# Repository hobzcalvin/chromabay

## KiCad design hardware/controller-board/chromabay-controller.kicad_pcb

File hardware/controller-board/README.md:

# ChromaBay Controller (rev A)

A battery-powered ESP32-S3 LED controller: USB-C charging with a power path, a 5 V / 2 A LED rail, 4 clock+data
outputs (or 8 single-wire), a PDM mic, a 6-axis IMU, a swappable JST-PH battery and solder-free push-in LED terminals, on
36 × 66 mm (1.6 mm, rounded nose) with the button, USB-C and power switch all at one end, flush with the case
face (the button and switch stick out past it on their own).
The design reasoning is in [DESIGN.md](DESIGN.md). **Interactive 3D mock:** [viewer/index.html](viewer/index.html)
(needs the model files; see "Regenerate").

**Status:** schematic complete and ERC-clean. **Board fully routed:** DRC shows 0 errors and 0 unrouted. The charger
and boost power stage is hand-laid-out with copper pours (`tools/power_layout.py`), and the rest is autorouted. See
DESIGN.md section 0g. Before ordering: review it in KiCad and check part rotations in JLC's 3D preview.

| | |
|---|---|
|  |  |
|  |  |

## Files

| Path | What |
|---|---|
| `chromabay-controller.kicad_pro/.kicad_sch/.kicad_pcb` | KiCad 9 project. Open the `.kicad_pro`. |
| `chromabay-controller-schematic.pdf` | Schematic PDF |
| `lib/lcsc.*` | Symbols, footprints and 3D models for the exact JLC/LCSC parts (via easyeda2kicad) |
| `lib/cb.pretty` | Board-specific footprints: LED output pads, battery pads |
| `tools/design.py` | **Single source of truth**: every part, LCSC code and net |
| `tools/outline.py` | Board outline (rounded nose, battery notch), shared by the board and the case |
| `tools/gen_sch.py`, `tools/gen_pcb.py` | Generate the schematic and the placed board from `design.py` |
| `tools/jlc_cost.py`, `tools/jlc_lookup.py` | Live JLC prices / Basic-vs-Extended status, and the order cost estimate |
| `tools/jlc_files.py` → `fab/` | JLC BOM + CPL for each build: `complete`, `plug`, `core` |
| `tools/cost_options.py` | What each optional feature costs per board |
| `case/case.py` → `case/out/*.stl` | Parametric clamshell case: `external`, `slim` (603450 cell), `thick` (103450 cell), `brick` (2 × 18650) |
| `tools/route.py` | Autoroute: GND fan-out, DSN export (In1 kept as plane), Freerouting 1.9, SES import, zone fill |
| `tools/power_layout.py` | Hand layout of the charger/boost power copper: pours, In2 plane regions, via arrays, short links |
| `tools/fix_silk.py` | Nudges user-header labels off vias, pads and part outlines on the routed board (re-run after regenerating) |
| `tools/fanout.py`, `tools/patch_route.py` | GND via fan-out; small maze router for leftover gaps (+ via merge) |
| `tools/label_render.py` | Labeled top-view render |
| `renders/` | Board renders (KiCad), labeled interaction-point view, case/battery renders (three.js) |
| `viewer/index.html` | Rotatable 3D mock: board + case variants + clickable connection markers |

## Regenerate

```sh
# KiCad 9 (kicad-cli + its python), easyeda2kicad, cadquery
python3 tools/gen_sch.py && kicad-cli sch erc ../chromabay-controller.kicad_sch   # from tools/
/usr/bin/python3 tools/gen_pcb.py        # KiCad's system python (has pcbnew)
python3 tools/jlc_files.py               # fab/bom-jlc.csv, fab/cpl-jlc.csv
python3 tools/jlc_cost.py 5 10 30        # live cost table
python3 case/case.py                     # case STLs (add STEP by editing the export list)
```

`gen_pcb.py` re-places everything, so **once routing starts, stop regenerating the PCB**: from then on, edit the
schematic in KiCad and use *Update PCB from Schematic*. The symbol/footprint UUID links already match.

## Before ordering

Ready to upload: `fab/gerbers-jlc.zip` (Gerbers + drill), `fab/bom-jlc-<build>.csv` and
`fab/cpl-jlc-<build>.csv` for the build you want (`complete`, `plug` or `core`). Regenerate the Gerbers after any
board edit (see DESIGN.md).

1. Look over the board in KiCad, especially the charger corner by the USB-C.
2. At JLC: 4 layers, 1.6 mm, tented vias, "Economic" PCBA on the top side. In the parts-placement preview, check
   **every** part's rotation and position. The easyeda2kicad parts are usually right, but the USB-C, slide
   switch, button, LED, WAGOs, JST, mic and the QFN/DFN power chips are the ones to look at.
3. Expect JLC to ask about the button and switch overhanging the board edge (on purpose) and the 0.35/0.2 mm
   REGN vias.
4. Boost compensation (15k / 4.7 nF / 47 pF) and current limit (200k) are checked by `tools/boost_loop.py` (the WEBENCH-equivalent loop analysis); no WEBENCH run needed.
5. Order 2–5 to validate. Tests: charge current per jumper setting, boost ripple and efficiency at 2 A, run while
   charging from a weak port, reverse-battery protection, 8 outputs, mic, IMU, deep-sleep current with the switch off.

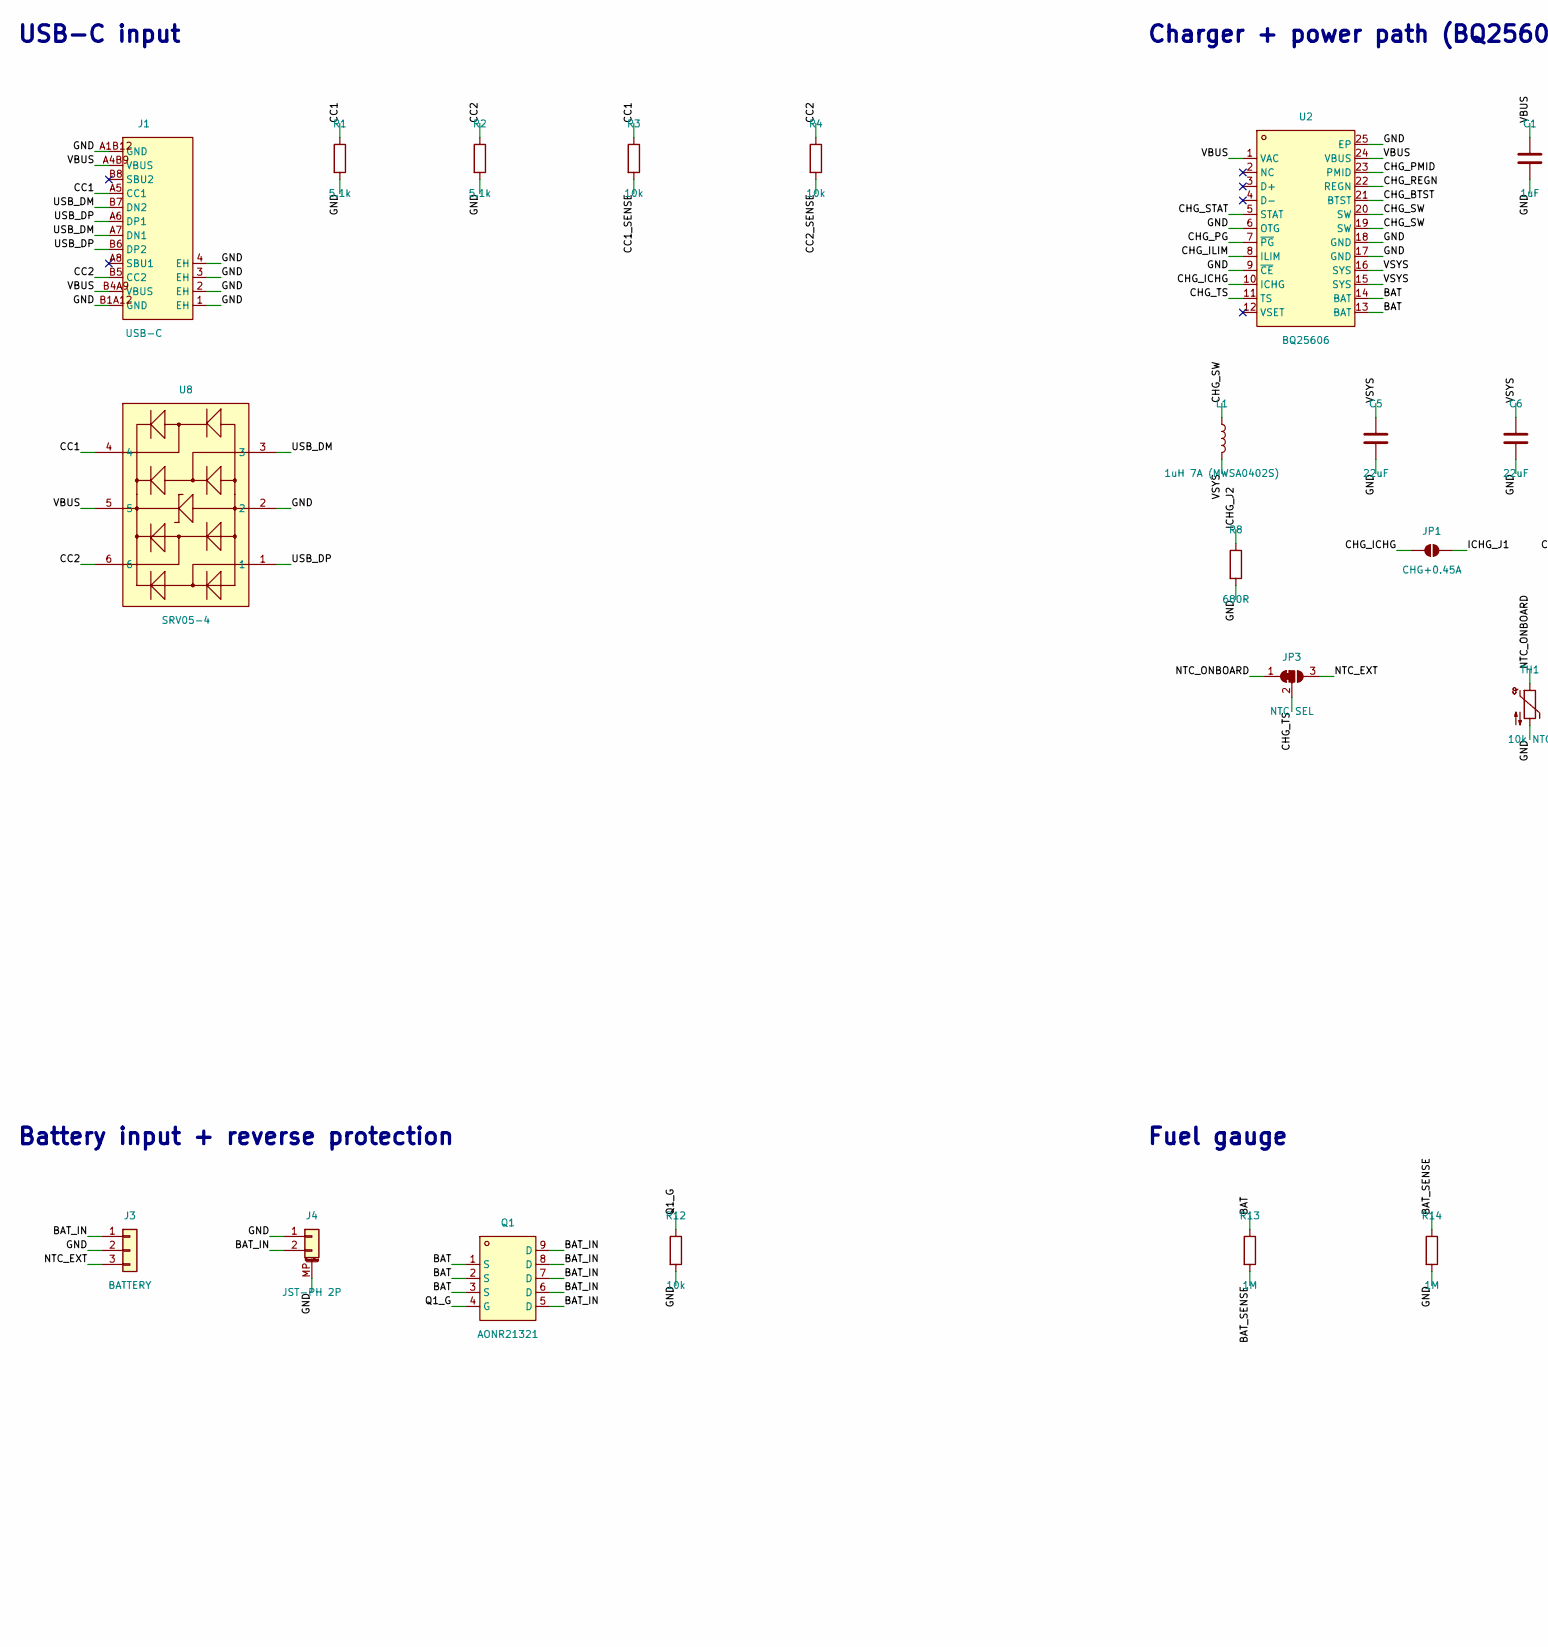
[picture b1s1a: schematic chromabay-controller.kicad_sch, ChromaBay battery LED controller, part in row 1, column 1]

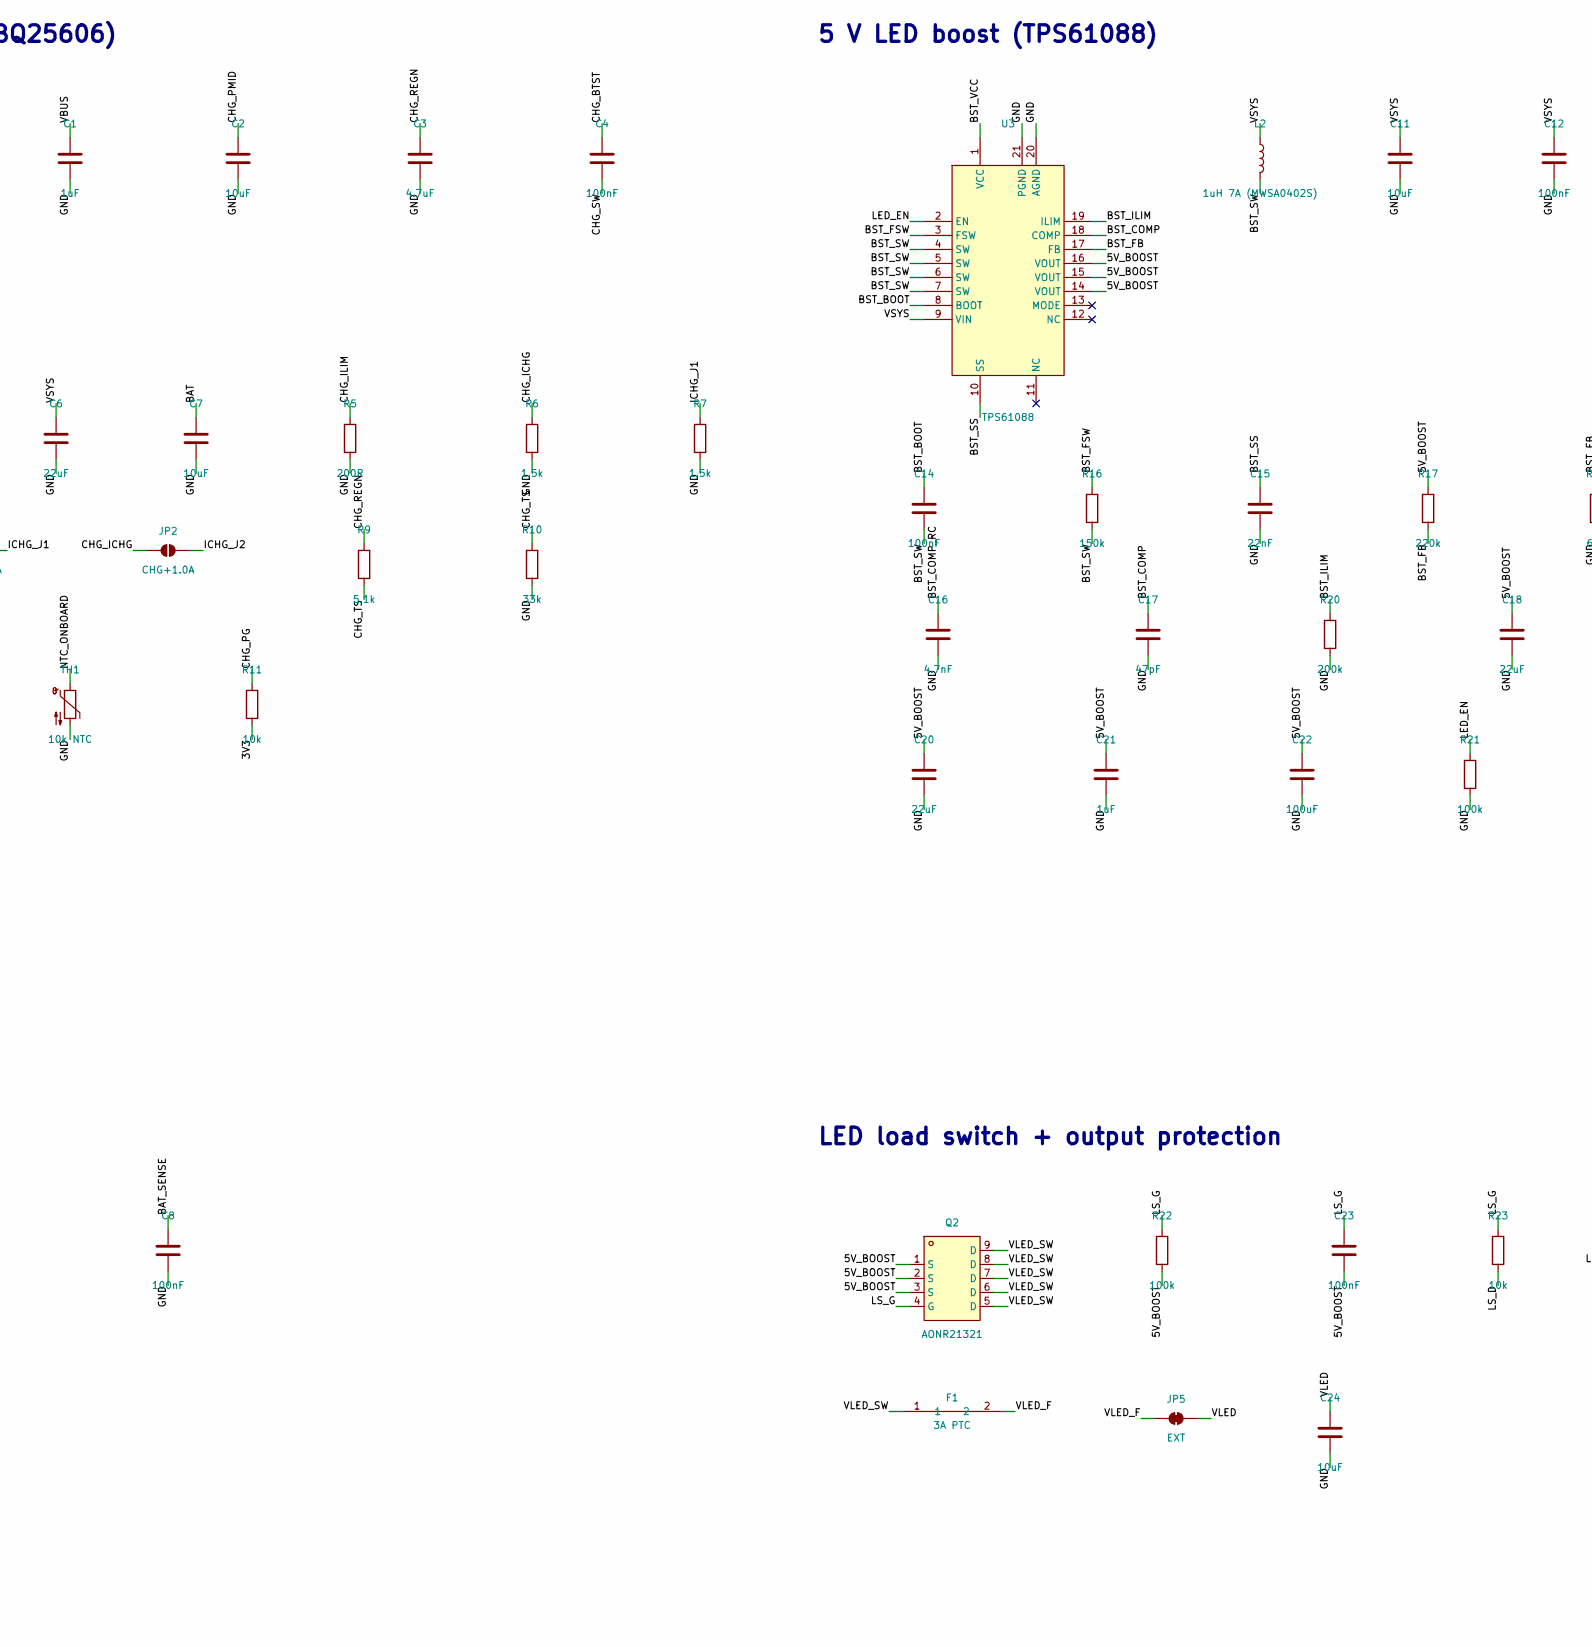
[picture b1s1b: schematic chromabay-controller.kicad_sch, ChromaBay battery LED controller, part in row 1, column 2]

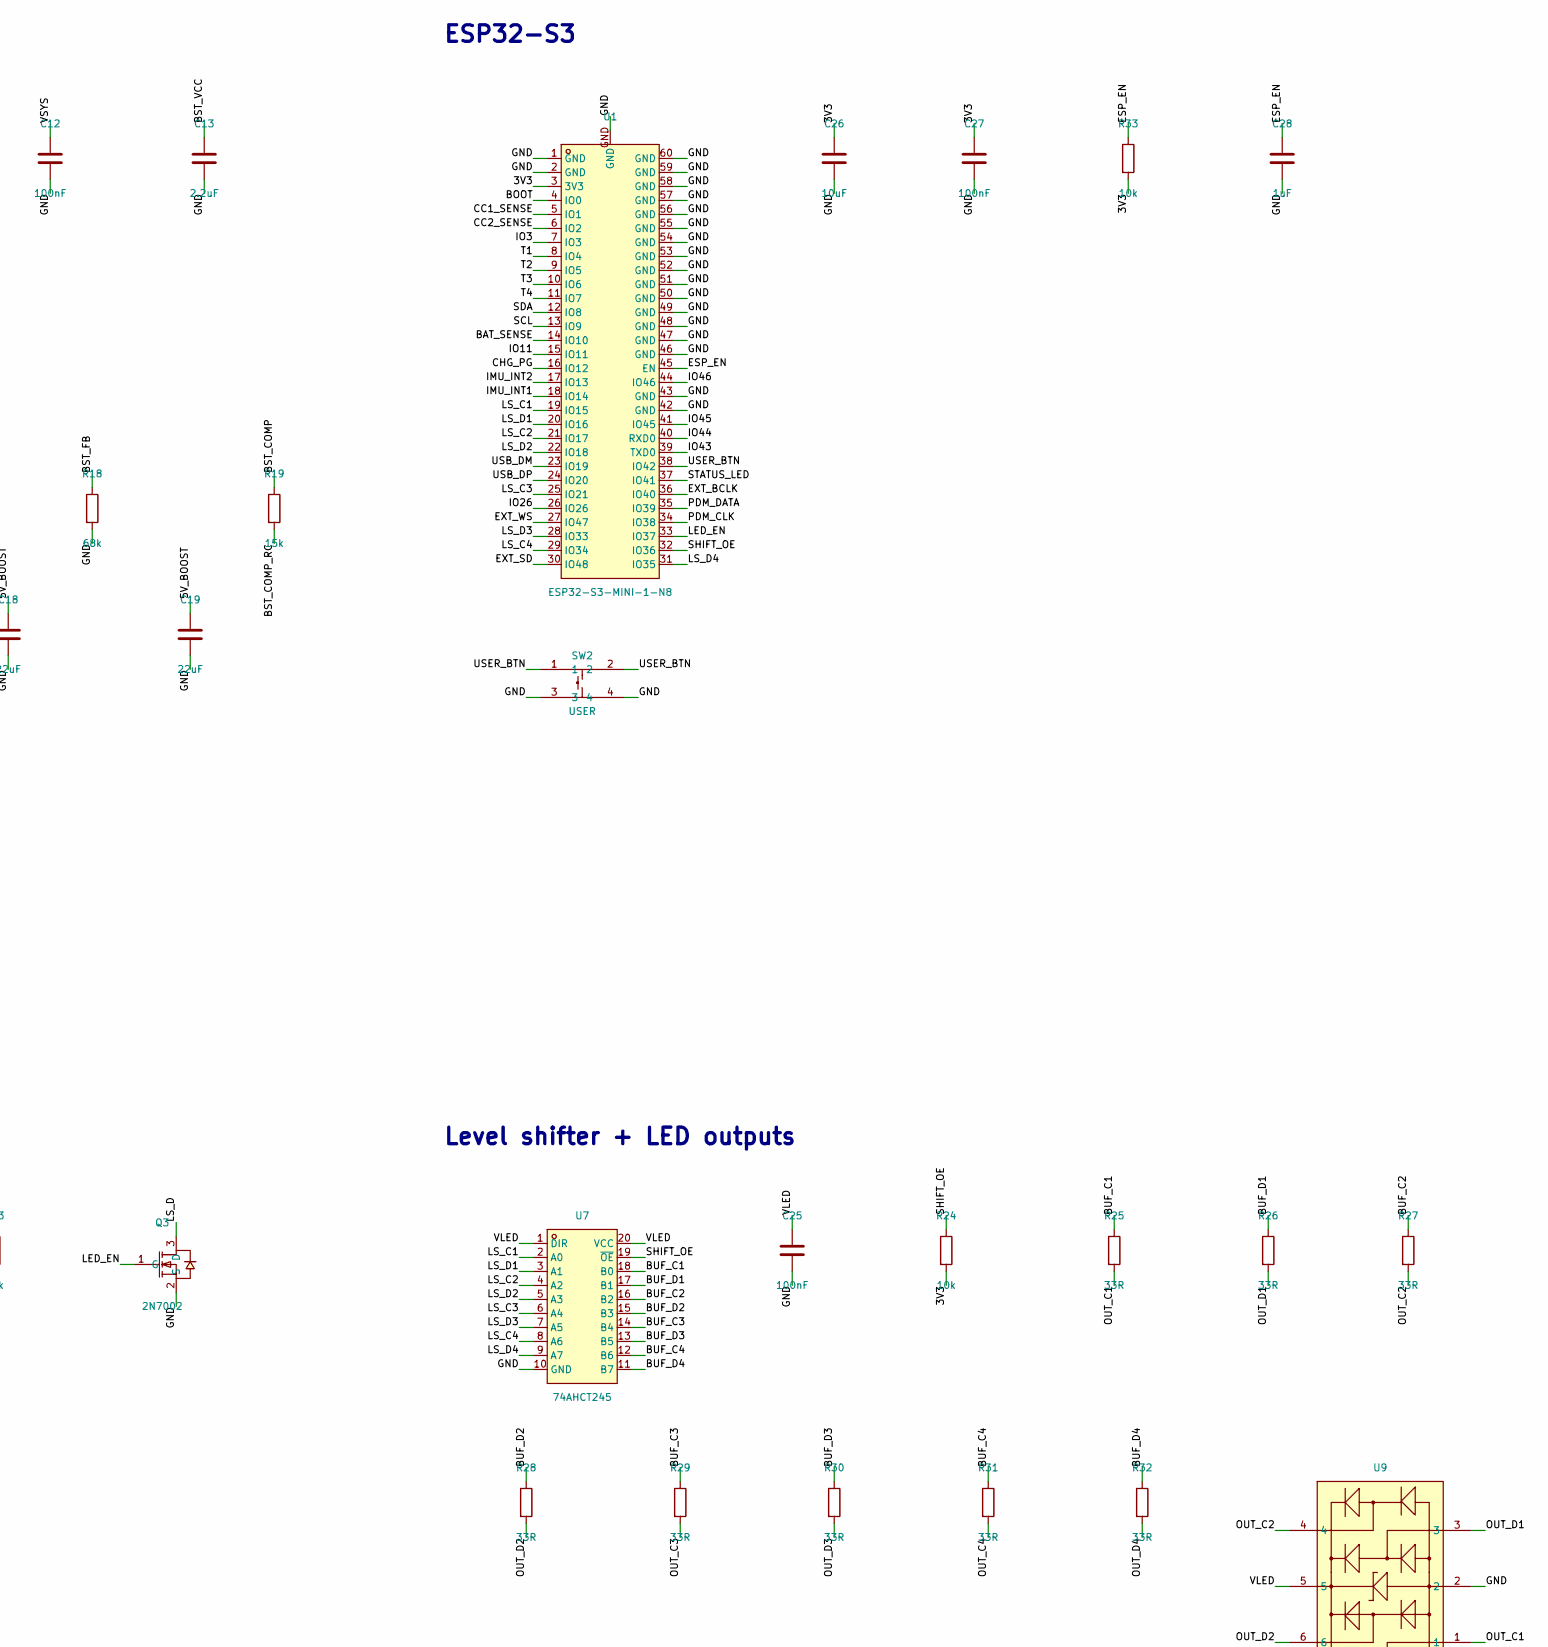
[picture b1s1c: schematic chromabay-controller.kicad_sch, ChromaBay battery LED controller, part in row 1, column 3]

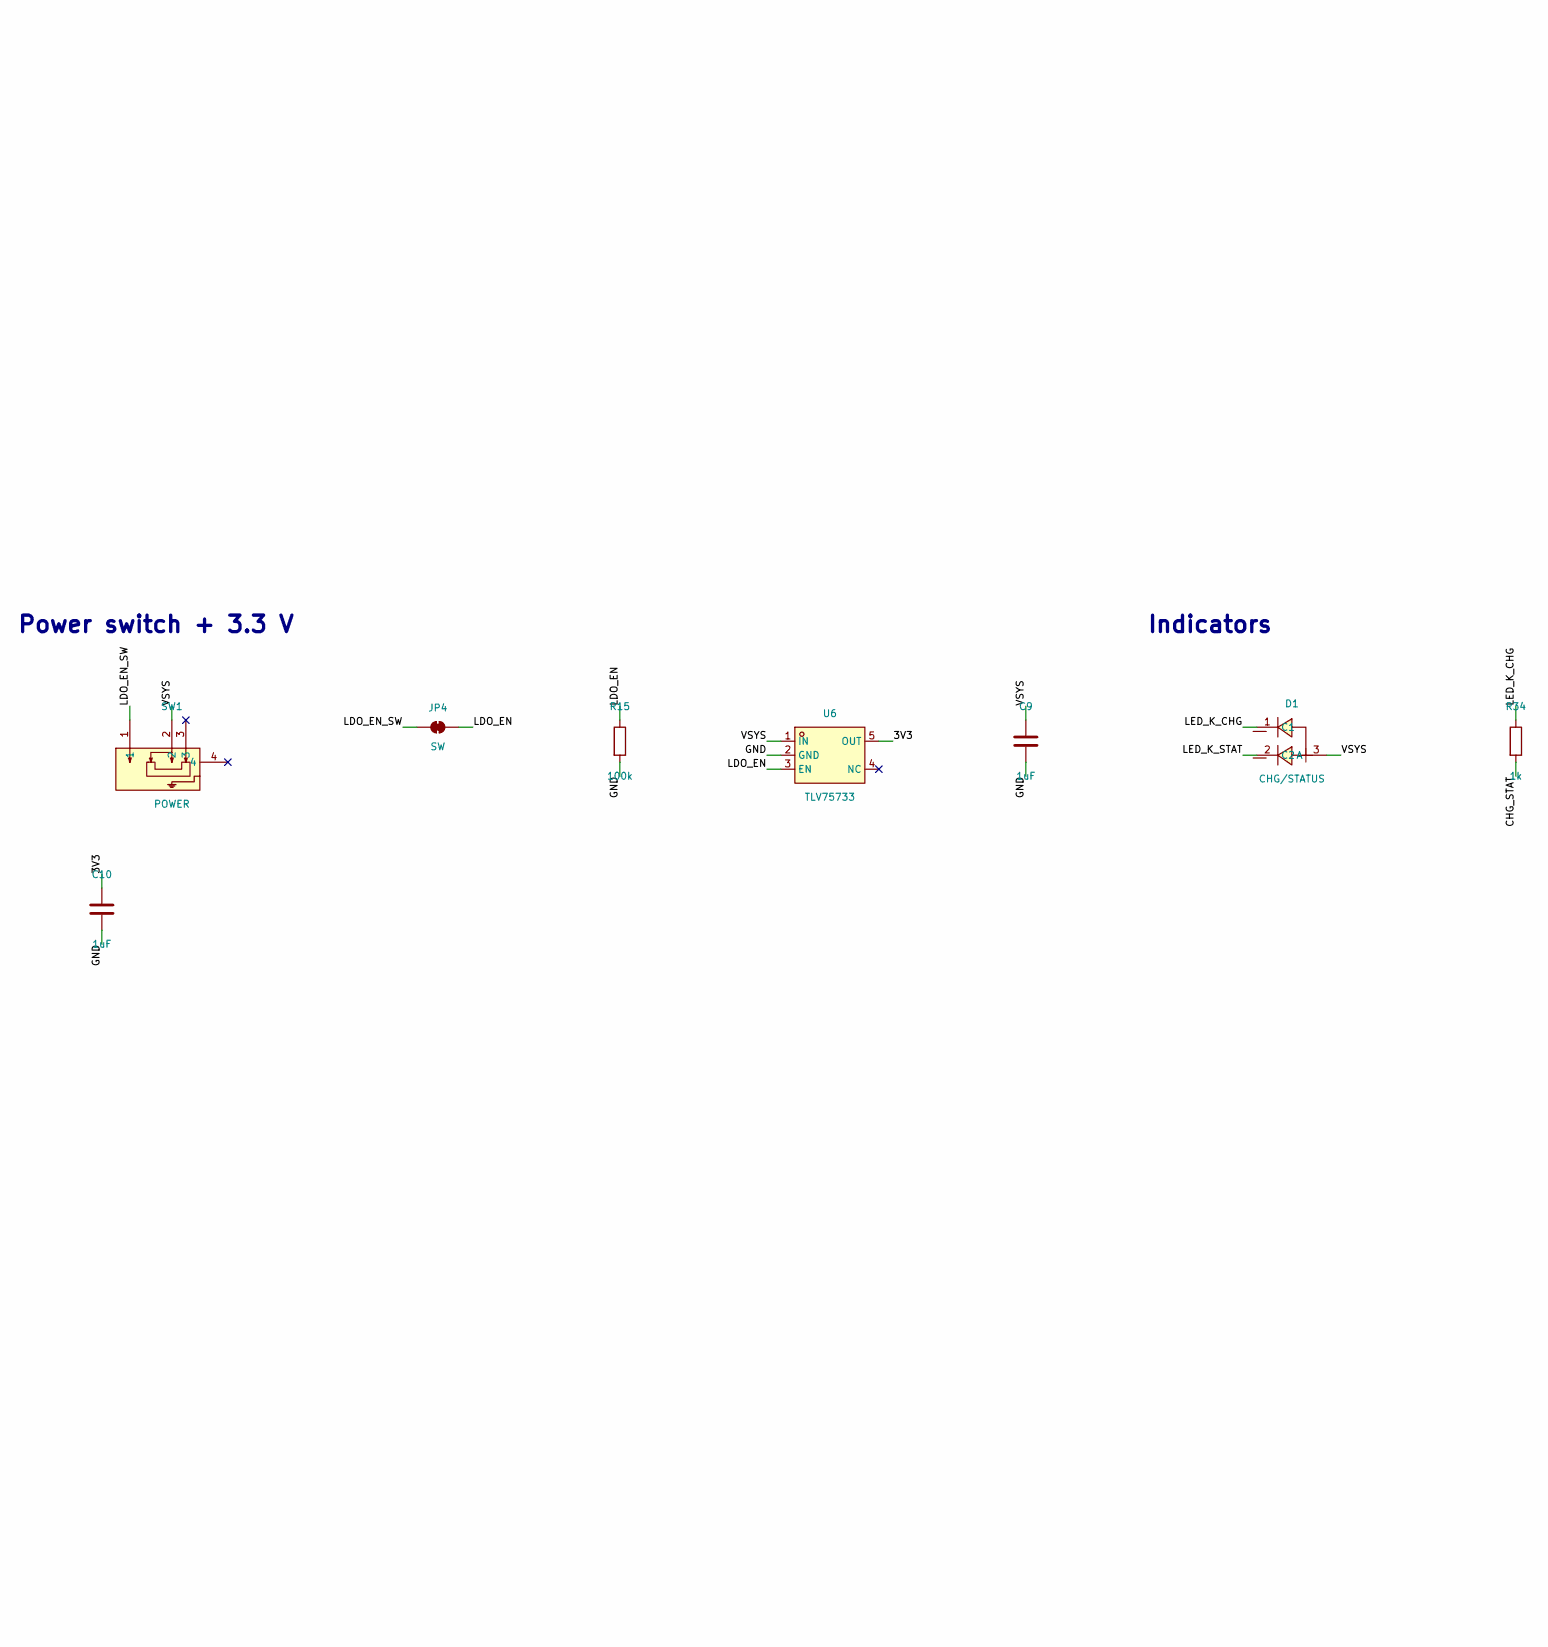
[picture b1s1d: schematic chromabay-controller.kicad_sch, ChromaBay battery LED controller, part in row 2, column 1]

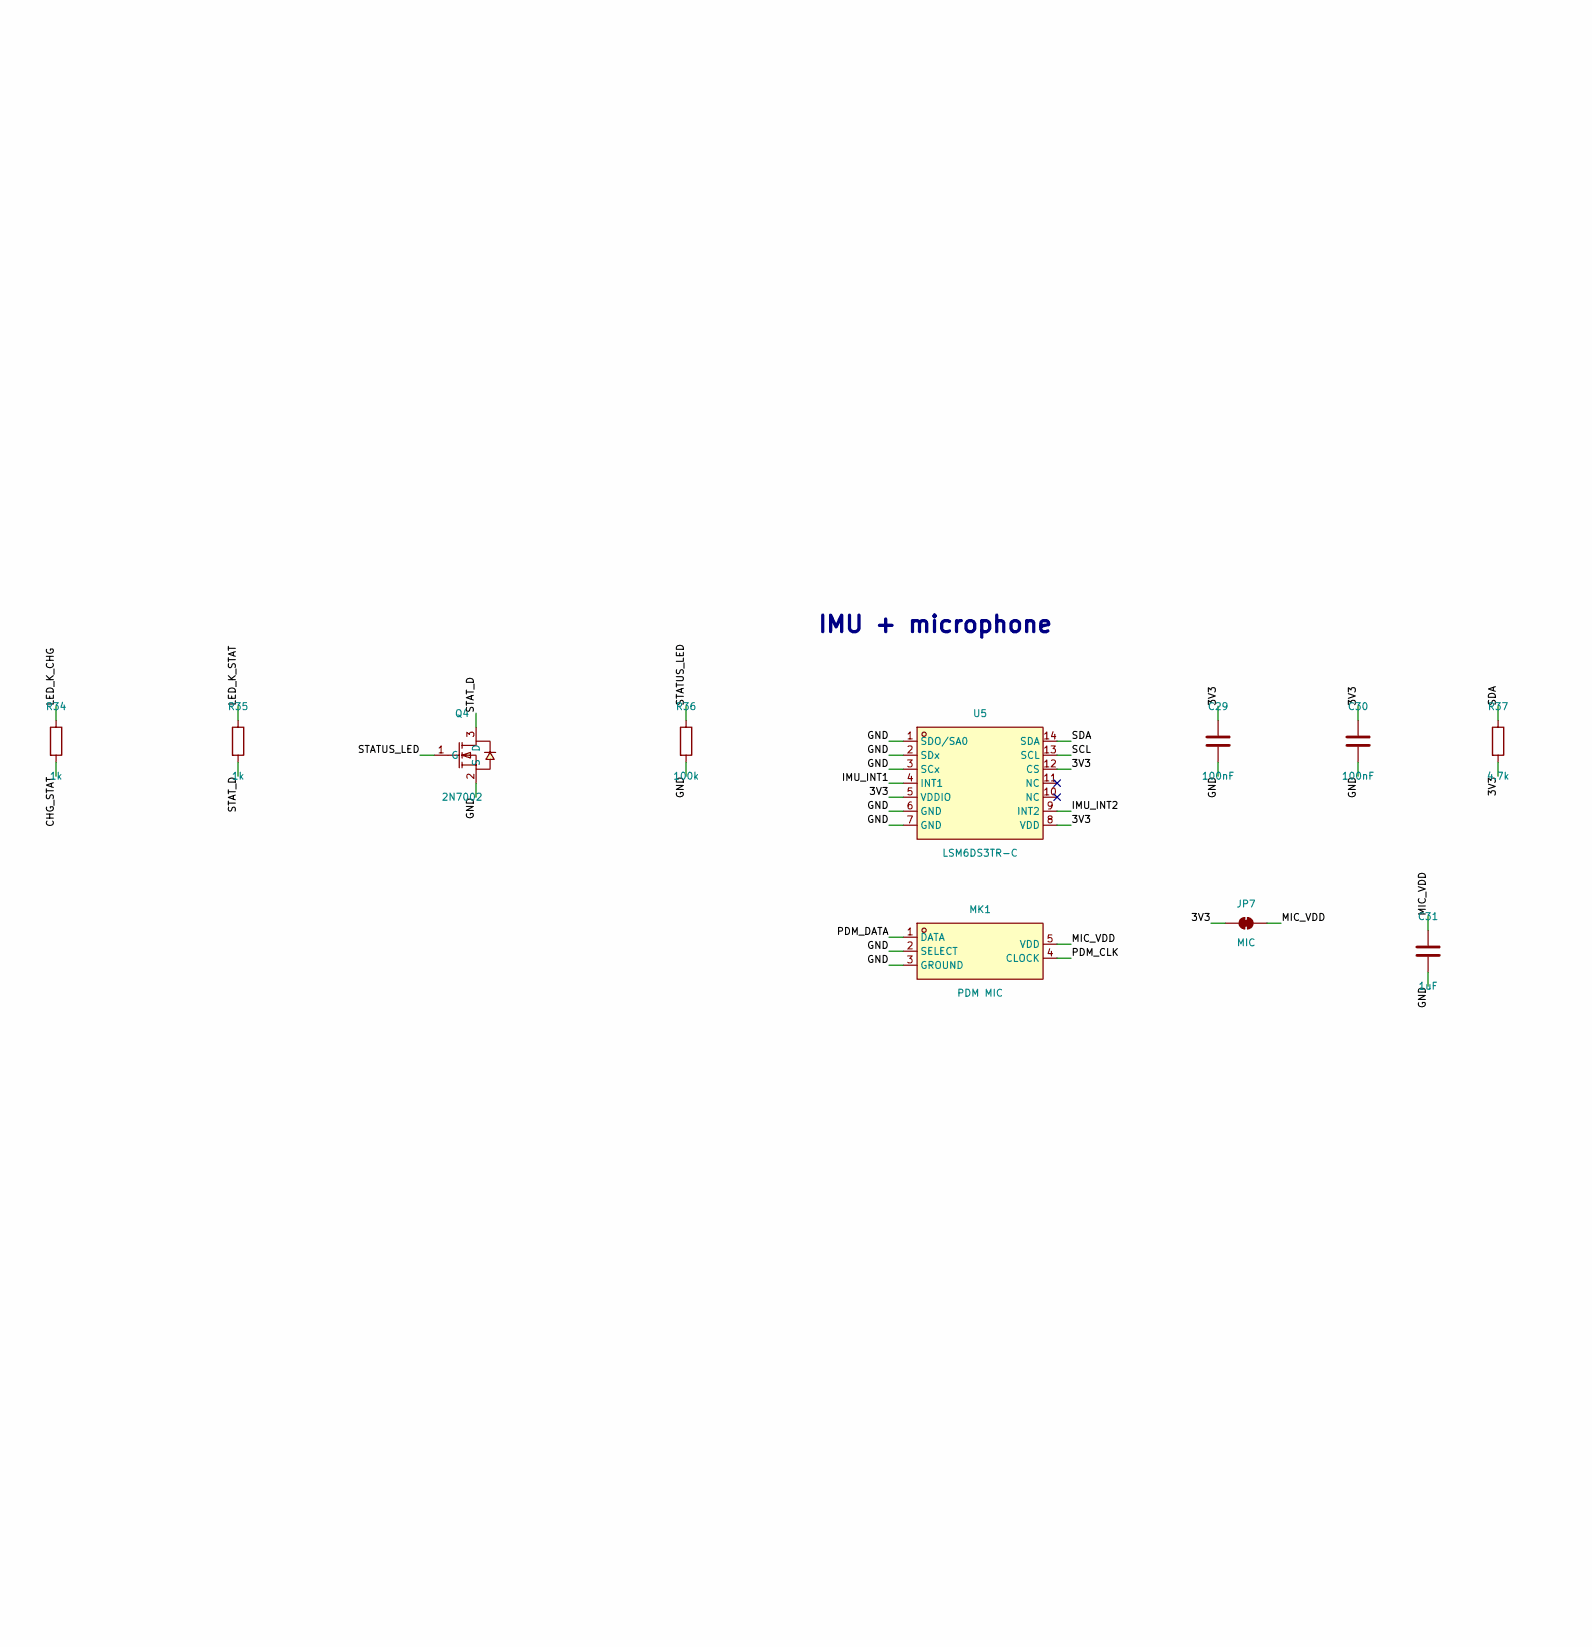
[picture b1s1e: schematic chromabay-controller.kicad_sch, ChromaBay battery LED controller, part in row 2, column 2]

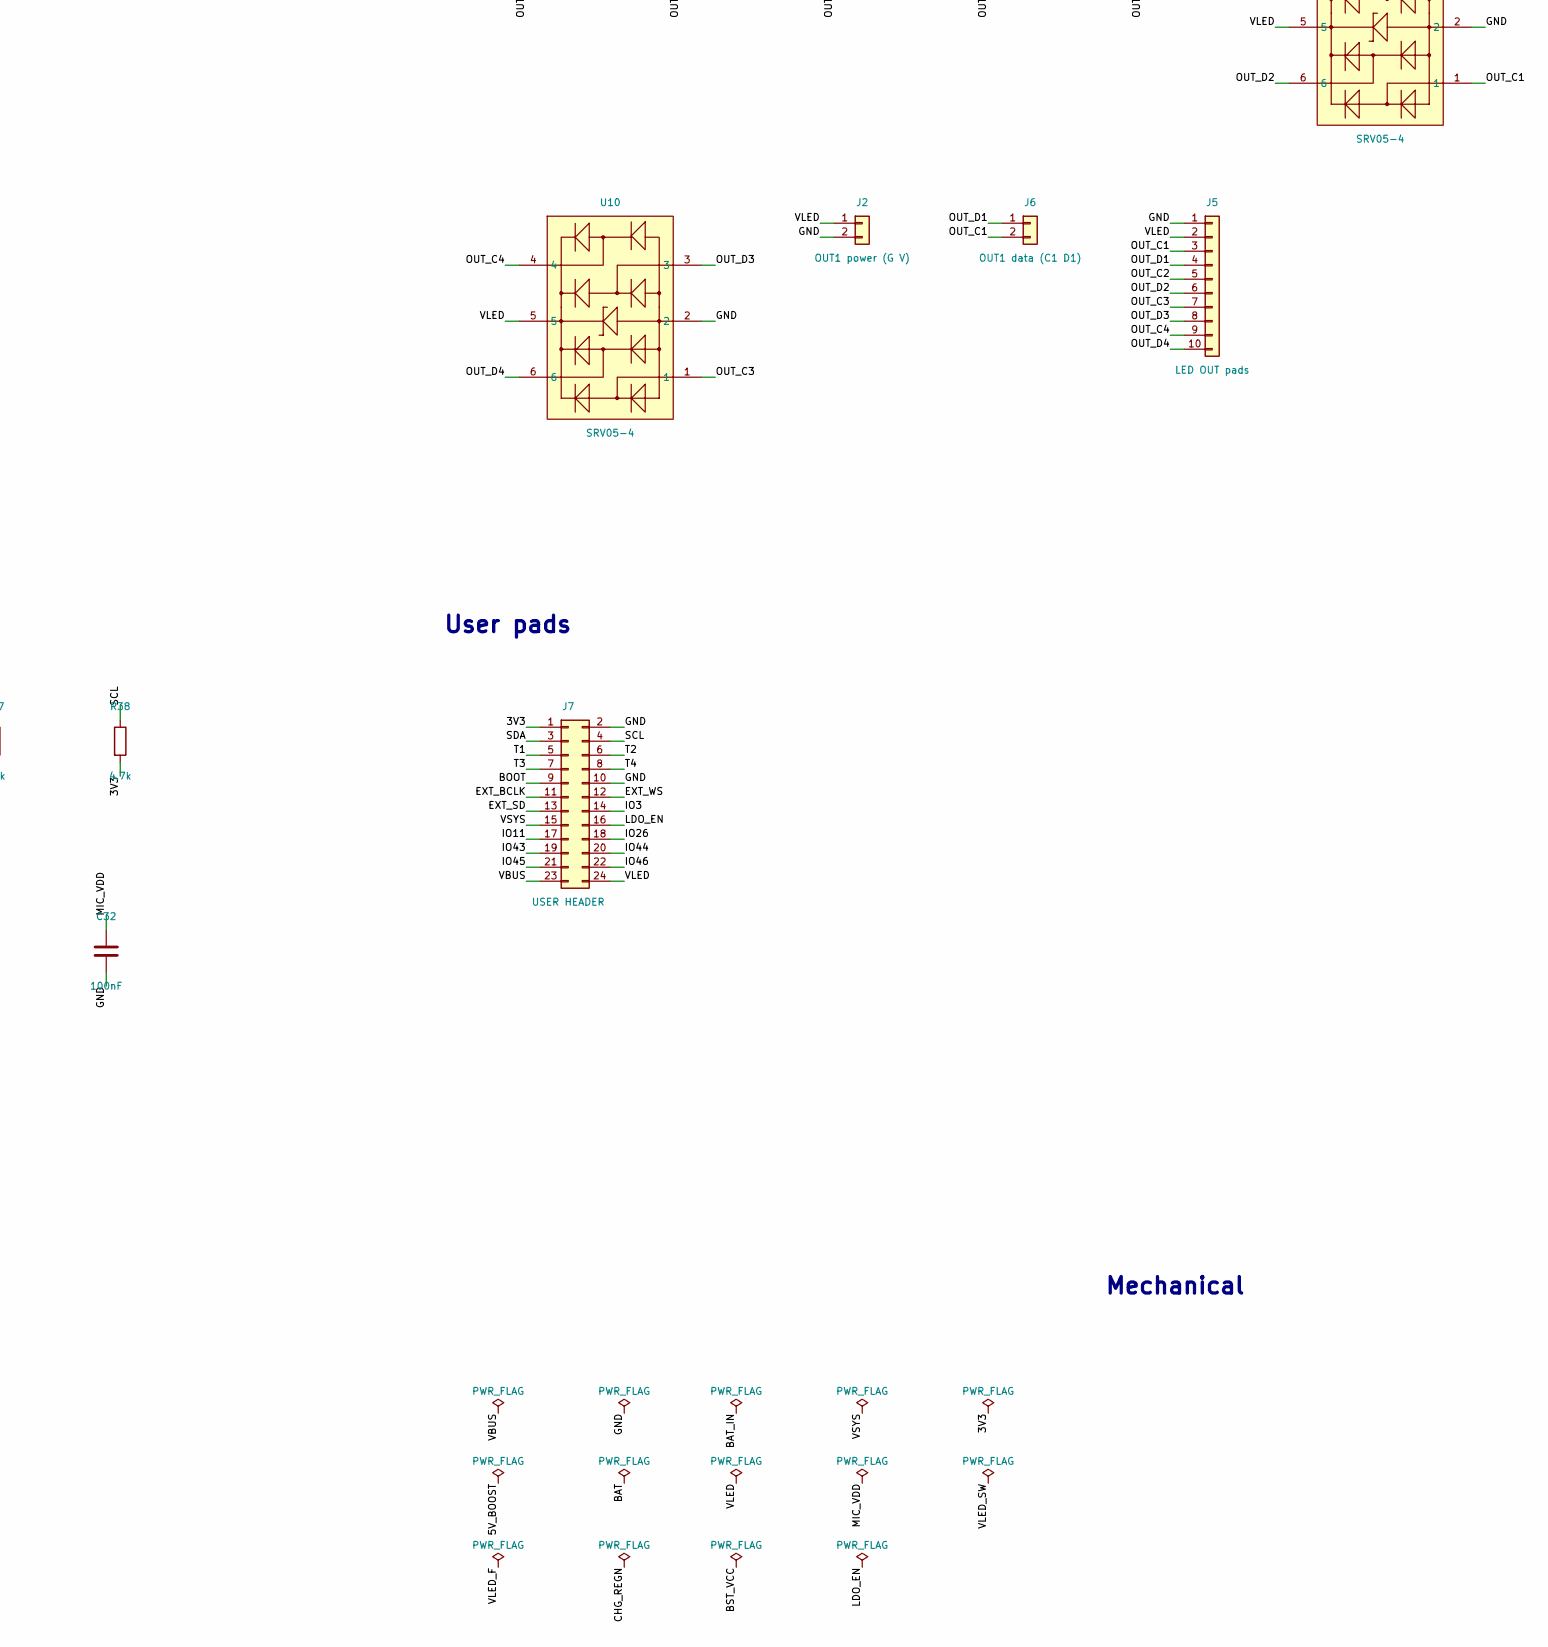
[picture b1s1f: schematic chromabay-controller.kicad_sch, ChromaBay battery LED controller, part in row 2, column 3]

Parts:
C1: 1uF; C0603; LCSC C15849
C2, C7, C11, C24: 10uF; C0805; LCSC C15850
C3: 4.7uF; C0603; LCSC C19666
C4, C8, C12, C14, C23, C25, C27, C29, C30, C32: 100nF; C0402; LCSC C1525
C5, C6, C18, C19, C20: 22uF; C0805; LCSC C45783
C9, C10, C21, C28, C31: 1uF; C0402; LCSC C52923
C13: 2.2uF; C0402; LCSC C12530
C15: 22nF; C0402; LCSC C1532
C16: 4.7nF; C0402; LCSC C1538
C17: 47pF; C0402; LCSC C1567
C22: 100uF; C1206; LCSC C15008
C26: 10uF; C0603; LCSC C19702
D1: CHG/STATUS; LED-SMD_LTST-S326KGJRKT; LCSC C125116
F1: 3A PTC; F1812; LCSC C21004
J1: USB-C; USB-C_SMD-TYPE-C-31-M-12_1; LCSC C165948
J2: OUT1 power (G V); CONN-SMD_2060-452; LCSC C2765055
J3: BATTERY; BatteryPadsSmall
J4: JST-PH 2P; CONN-SMD_P2.00_S2B-PH-SM4-TB-LF-SN; LCSC C54582899
J5: LED OUT pads; OutputPads
J6: OUT1 data (C1 D1); CONN-SMD_2060-452; LCSC C2765055
J7: USER HEADER; PinHeader_2x12_P2.54mm_Vertical
JP1: CHG+0.45A; SolderJumper-2_P1.3mm_Open_RoundedPad1.0x1.5mm
JP2: CHG+1.0A; SolderJumper-2_P1.3mm_Open_RoundedPad1.0x1.5mm
JP3: NTC SEL; SolderJumper-3_P1.3mm_Bridged12_RoundedPad1.0x1.5mm
JP4: SW; SolderJumper-2_P1.3mm_Bridged_RoundedPad1.0x1.5mm
JP5: EXT; SolderJumper-2_P1.3mm_Bridged_RoundedPad1.0x1.5mm
JP7: MIC; SolderJumper-2_P1.3mm_Bridged_RoundedPad1.0x1.5mm
L1, L2: 1uH 7A (MWSA0402S); IND-SMD_L4.4-W4.2; LCSC C408332
MK1: PDM MIC; MIC-SMD_GMA3526H10-B26; LCSC C498192
Q1, Q2: AONR21321; DFN-8_L3.0-W3.0-P0.65-BL; LCSC C541711
Q3, Q4: 2N7002; SOT-23-3_L2.9-W1.3-P1.90-LS2.4-BR; LCSC C8545
R1, R2, R9: 5.1k; R0402; LCSC C25905
R3, R4, R11, R12, R23, R24, R33: 10k; R0402; LCSC C25744
R5: 200R; R0402; LCSC C25087
R6, R7: 1.5k; R0402; LCSC C25867
R8: 680R; R0402; LCSC C25130
R10: 33k; R0402; LCSC C25779
R13, R14: 1M; R0402; LCSC C26083
R15, R21, R22, R36: 100k; R0402; LCSC C25741
R16: 150k; R0402; LCSC C25755
R17: 220k; R0402; LCSC C25767
R18: 68k; R0402; LCSC C36871
R19: 15k; R0402; LCSC C25756
R20: 200k; R0402; LCSC C25764
R25, R26, R27, R28, R29, R30, R31, R32: 33R; R0402; LCSC C25105
R34, R35: 1k; R0402; LCSC C11702
R37, R38: 4.7k; R0402; LCSC C25900
SW1: POWER; SW-TH_MSK12C02; LCSC C431540
SW2: USER; KEY-SMD_4P-L4.8-W4.6-P1.70-LS6.2; LCSC C136662
TH1: 10k NTC; R0402; LCSC C77131
U1: ESP32-S3-MINI-1-N8; BULETM-SMD_ESP32-S3-MINI-1-N8; LCSC C2913206
U2: BQ25606; VQFN-24_L4.0-W4.0-P0.50-TL-EP2.8; LCSC C374063
U3: TPS61088; VQFN-20_L4.6-W3.6-P0.50-BL; LCSC C87357
U5: LSM6DS3TR-C; LGA-14_L3.0-W2.5-P0.50-TL; LCSC C967633
U6: TLV75733; SOT-23-5_L2.9-W1.6-P0.95-LS2.8-BL; LCSC C485517
U7: 74AHCT245; TSSOP-20_L6.5-W4.4-P0.65-LS6.4-BL; LCSC C54815895
U8, U9, U10: SRV05-4; SOT-23-6_L2.9-W1.6-P0.95-LS2.8-BR; LCSC C85364

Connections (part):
/3V3: C10.1, C26.1, C27.1, C29.1, C30.1, J7.1, JP7.1 (A), R11.2, R24.2, R33.2, R37.2, R38.2, U1.3 (3V3), U5.5 (VDDIO), U5.8 (VDD), U5.12 (CS), U6.5 (OUT)
/5V_BOOST: C18.1, C19.1, C20.1, C21.1, C22.1, C23.2, Q2.1 (S), Q2.2 (S), Q2.3 (S), R17.1, R22.2, U3.14 (VOUT), U3.15 (VOUT), U3.16 (VOUT)
/BAT: C7.1, Q1.1 (S), Q1.2 (S), Q1.3 (S), R13.1, U2.13 (BAT), U2.14 (BAT)
/BAT_IN: J3.1, J4.2, Q1.5 (D), Q1.6 (D), Q1.7 (D), Q1.8 (D), Q1.9 (D)
/BAT_SENSE: C8.1, R13.2, R14.1, U1.14 (IO10)
/BOOT: J7.9, U1.4 (IO0)
/BST_BOOT: C14.1, U3.8 (BOOT)
/BST_COMP: C17.1, R19.1, U3.18 (COMP)
/BST_COMP_RC: C16.1, R19.2
/BST_FB: R17.2, R18.1, U3.17 (FB)
/BST_FSW: R16.1, U3.3 (FSW)
/BST_ILIM: R20.1, U3.19 (ILIM)
/BST_SS: C15.1, U3.10 (SS)
/BST_SW: C14.2, L2.2, R16.2, U3.4 (SW), U3.5 (SW), U3.6 (SW), U3.7 (SW)
/BST_VCC: C13.1, U3.1 (VCC)
/BUF_C1: R25.1, U7.18 (B0)
/BUF_C2: R27.1, U7.16 (B2)
/BUF_C3: R29.1, U7.14 (B4)
/BUF_C4: R31.1, U7.12 (B6)
/BUF_D1: R26.1, U7.17 (B1)
/BUF_D2: R28.1, U7.15 (B3)
/BUF_D3: R30.1, U7.13 (B5)
/BUF_D4: R32.1, U7.11 (B7)
/CC1: J1.A5 (CC1), R1.1, R3.1, U8.4
/CC1_SENSE: R3.2, U1.5 (IO1)
/CC2: J1.B5 (CC2), R2.1, R4.1, U8.6
/CC2_SENSE: R4.2, U1.6 (IO2)
/CHG_BTST: C4.1, U2.21 (BTST)
/CHG_ICHG: JP1.1 (A), JP2.1 (A), R6.1, U2.10 (ICHG)
/CHG_ILIM: R5.1, U2.8 (ILIM)
/CHG_PG: R11.1, U1.16 (IO12), U2.7 (~PG)
/CHG_PMID: C2.1, U2.23 (PMID)
/CHG_REGN: C3.1, R9.1, U2.22 (REGN)
/CHG_STAT: R34.2, U2.5 (STAT)
/CHG_SW: C4.2, L1.1, U2.19 (SW), U2.20 (SW)
/CHG_TS: JP3.2 (C), R9.2, R10.1, U2.11 (TS)
/ESP_EN: C28.1, R33.1, U1.45 (EN)
/EXT_BCLK: J7.11, U1.36 (IO40)
/EXT_SD: J7.13, U1.30 (IO48)
/EXT_WS: J7.12, U1.27 (IO47)
/GND: C1.2, C2.2, C3.2, C5.2, C6.2, C7.2, C8.2, C9.2, C10.2, C11.2, C12.2, C13.2, C15.2, C16.2, C17.2, C18.2, C19.2, C20.2, C21.2, C22.2, C24.2, C25.2, C26.2, C27.2, C28.2, C29.2, C30.2, C31.2, C32.2, J1.1 (EH), J1.2 (EH), J1.3 (EH), J1.4 (EH), J1.A1B12 (GND), J1.B1A12 (GND), J2.2, J3.2, J4.1, J4.MP (MountPin), J5.1, J7.2, J7.10, MK1.2 (SELECT), MK1.3 (GROUND), Q3.2 (S), Q4.2 (S), R1.2, R2.2, R5.2, R6.2, R7.2, R8.2, R10.2, R12.2, R14.2, R15.2, R18.2, R20.2, R21.2, R36.2, SW2.3, SW2.4, TH1.2, U1.1 (GND), U1.2 (GND), U1.42 (GND), U1.43 (GND), U1.46 (GND), U1.47 (GND), U1.48 (GND), U1.49 (GND), U1.50 (GND), U1.51 (GND), U1.52 (GND), U1.53 (GND), U1.54 (GND), U1.55 (GND), U1.56 (GND), U1.57 (GND), U1.58 (GND), U1.59 (GND), U1.60 (GND), U1.GND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
/ICHG_J1: JP1.2 (B), R7.1
/ICHG_J2: JP2.2 (B), R8.1
/IMU_INT1: U1.18 (IO14), U5.4 (INT1)
/IMU_INT2: U1.17 (IO13), U5.9 (INT2)
/IO3: J7.14, U1.7 (IO3)
/IO11: J7.17, U1.15 (IO11)
/IO26: J7.18, U1.26 (IO26)
/IO43: J7.19, U1.39 (TXD0)
/IO44: J7.20, U1.40 (RXD0)
/IO45: J7.21, U1.41 (IO45)
/IO46: J7.22, U1.44 (IO46)
/LDO_EN: J7.16, JP4.2 (B), R15.1, U6.3 (EN)
/LDO_EN_SW: JP4.1 (A), SW1.1
/LED_EN: Q3.1 (G), R21.1, U1.33 (IO37), U3.2 (EN)
/LED_K_CHG: D1.1 (C1), R34.1
/LED_K_STAT: D1.2 (C2), R35.1
/LS_C1: U1.19 (IO15), U7.2 (A0)
/LS_C2: U1.21 (IO17), U7.4 (A2)
/LS_C3: U1.25 (IO21), U7.6 (A4)
/LS_C4: U1.29 (IO34), U7.8 (A6)
/LS_D: Q3.3 (D), R23.2
/LS_D1: U1.20 (IO16), U7.3 (A1)
/LS_D2: U1.22 (IO18), U7.5 (A3)
/LS_D3: U1.28 (IO33), U7.7 (A5)
/LS_D4: U1.31 (IO35), U7.9 (A7)
/LS_G: C23.1, Q2.4 (G), R22.1, R23.1
/MIC_VDD: C31.1, C32.1, JP7.2 (B), MK1.5 (VDD)
/NTC_EXT: J3.3, JP3.3 (B)
/NTC_ONBOARD: JP3.1 (A), TH1.1
/OUT_C1: J5.3, J6.2, R25.2, U9.1
/OUT_C2: J5.5, R27.2, U9.4
/OUT_C3: J5.7, R29.2, U10.1
/OUT_C4: J5.9, R31.2, U10.4
/OUT_D1: J5.4, J6.1, R26.2, U9.3
/OUT_D2: J5.6, R28.2, U9.6
/OUT_D3: J5.8, R30.2, U10.3
/OUT_D4: J5.10, R32.2, U10.6
/PDM_CLK: MK1.4 (CLOCK), U1.34 (IO38)
/PDM_DATA: MK1.1 (DATA), U1.35 (IO39)
/Q1_G: Q1.4 (G), R12.1
/SCL: J7.4, R38.1, U1.13 (IO9), U5.13 (SCL)
/SDA: J7.3, R37.1, U1.12 (IO8), U5.14 (SDA)
/SHIFT_OE: R24.1, U1.32 (IO36), U7.19 (~OE)
/STATUS_LED: Q4.1 (G), R36.1, U1.37 (IO41)
/STAT_D: Q4.3 (D), R35.2
/T1: J7.5, U1.8 (IO4)
/T2: J7.6, U1.9 (IO5)
/T3: J7.7, U1.10 (IO6)
/T4: J7.8, U1.11 (IO7)
/USB_DM: J1.A7 (DN1), J1.B7 (DN2), U1.23 (IO19), U8.3
/USB_DP: J1.A6 (DP1), J1.B6 (DP2), U1.24 (IO20), U8.1
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
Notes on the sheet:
USB-C input
Charger + power path (BQ25606)
Battery input + reverse protection
Fuel gauge
Power switch + 3.3 V
5 V LED boost (TPS61088)
LED load switch + output protection
Level shifter + LED outputs
ESP32-S3
Indicators
IMU + microphone
User pads
Mechanical

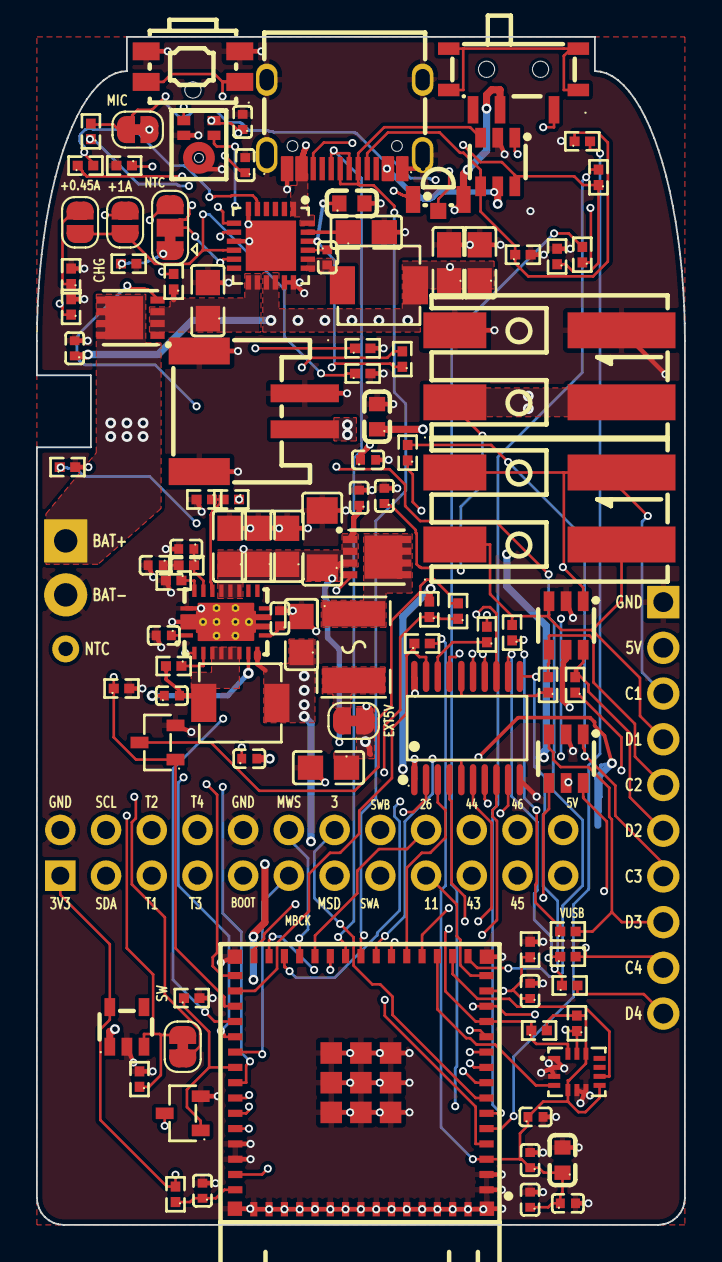
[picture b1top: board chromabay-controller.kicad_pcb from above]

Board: 4 copper layers, 36.0 x 66.0 mm, 104 parts (0 on the bottom side), 98 nets.

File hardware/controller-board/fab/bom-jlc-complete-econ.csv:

Comment,Designator,Footprint,LCSC Part #
USB-C,J1,USB-C_SMD-TYPE-C-31-M-12_1,C165948
5.1k,"R1,R2,R9",R0402,C25905
10k,"R3,R4,R11,R12,R23,R24,R33",R0402,C25744
SRV05-4,"U8,U9,U10",SOT-23-6_L2.9-W1.6-P0.95-LS2.8-BR,C85364
BQ25606,U2,VQFN-24_L4.0-W4.0-P0.50-TL-EP2.8,C374063
1uF,C1,C0603,C15849
10uF,"C2,C7,C11,C24",C0805,C15850
4.7uF,C3,C0603,C19666
100nF,"C4,C8,C12,C14,C23,C25,C27,C29,C30,C32",C0402,C1525
1uH 7A (MWSA0402S),"L1,L2",IND-SMD_L4.4-W4.2,C408332
22uF,"C5,C6,C18,C19,C20",C0805,C45783
200R,R5,R0402,C25087
1.5k,"R6,R7",R0402,C25867
680R,R8,R0402,C25130
33k,R10,R0402,C25779
10k NTC,TH1,R0402,C77131
JST-PH 2P,J4,CONN-SMD_P2.00_S2B-PH-SM4-TB-LF-SN,C54582899
AONR21321,"Q1,Q2",DFN-8_L3.0-W3.0-P0.65-BL,C541711
1M,"R13,R14",R0402,C26083
100k,"R15,R21,R22,R36",R0402,C25741
TLV75733,U6,SOT-23-5_L2.9-W1.6-P0.95-LS2.8-BL,C485517
1uF,"C9,C10,C21,C28,C31",C0402,C52923
TPS61088,U3,VQFN-20_L4.6-W3.6-P0.50-BL,C87357
2.2uF,C13,C0402,C12530
150k,R16,R0402,C25755
22nF,C15,C0402,C1532
220k,R17,R0402,C25767
68k,R18,R0402,C36871
15k,R19,R0402,C25756
4.7nF,C16,C0402,C1538
47pF,C17,C0402,C1567
200k,R20,R0402,C25764
100uF,C22,C1206,C15008
2N7002,"Q3,Q4",SOT-23-3_L2.9-W1.3-P1.90-LS2.4-BR,C8545
3A PTC,F1,F1812,C21004
74AHCT245,U7,TSSOP-20_L6.5-W4.4-P0.65-LS6.4-BL,C54815895
33R,"R25,R26,R27,R28,R29,R30,R31,R32",R0402,C25105
OUT1 power (G V),J2,CONN-SMD_2060-452,C2765055
OUT1 data (C1 D1),J6,CONN-SMD_2060-452,C2765055
ESP32-S3-MINI-1-N8,U1,BULETM-SMD_ESP32-S3-MINI-1-N8,C2913206
10uF,C26,C0603,C19702
USER,SW2,KEY-SMD_4P-L4.8-W4.6-P1.70-LS6.2,C136662
CHG/STATUS,D1,LED-SMD_LTST-S326KGJRKT,C125116
1k,"R34,R35",R0402,C11702
LSM6DS3TR-C,U5,LGA-14_L3.0-W2.5-P0.50-TL,C967633
4.7k,"R37,R38",R0402,C25900
PDM MIC,MK1,MIC-SMD_GMA3526H10-B26,C498192
